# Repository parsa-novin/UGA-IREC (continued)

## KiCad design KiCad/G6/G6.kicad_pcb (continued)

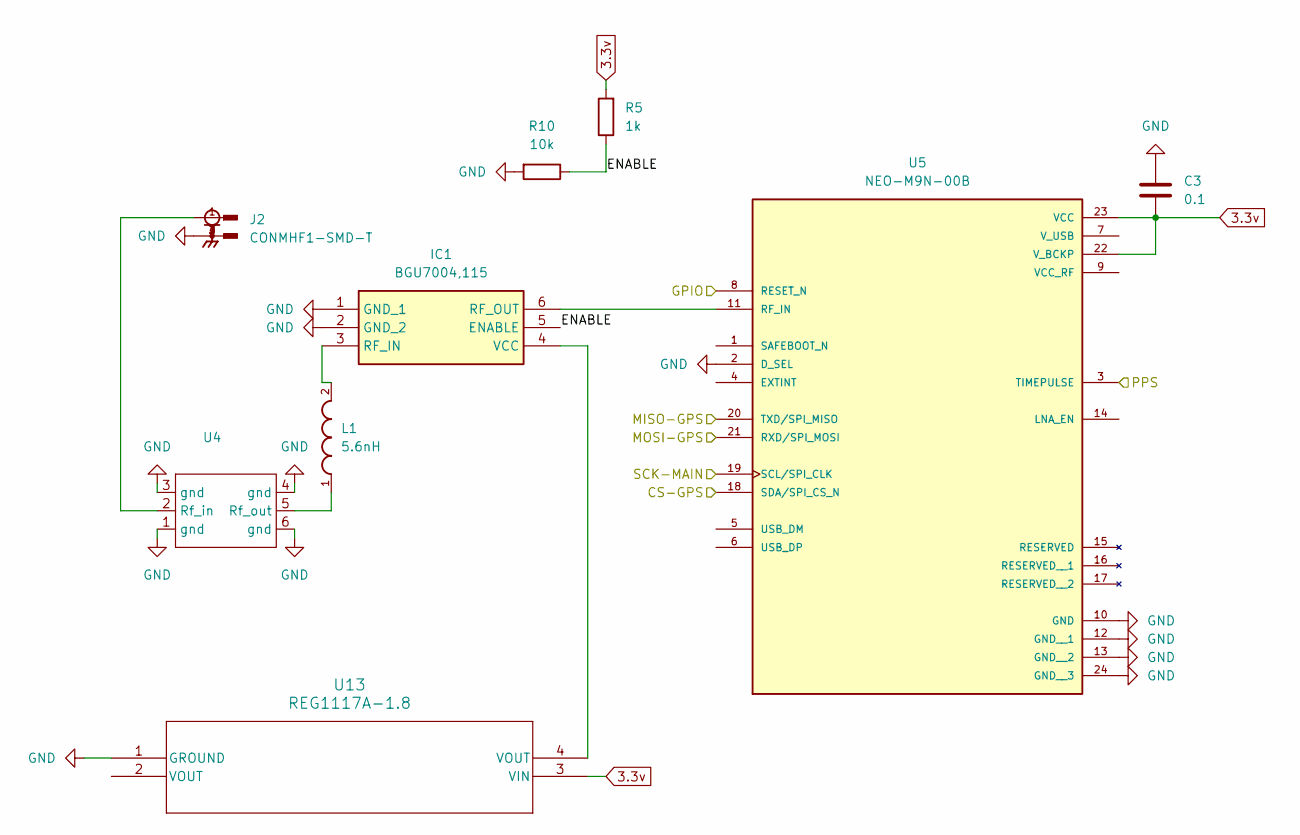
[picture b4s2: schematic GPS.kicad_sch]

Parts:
C3: 0.1; .1CAP_CC1206_YAG
IC1: BGU7004,115; BGU7004115; Manufacturer_Part_Number BGU7004,115; Mouser Part Number 771-BGU7004,115
J2: CONMHF1-SMD-T; TE_CONMHF1-SMD-T; PARTREV 09/22
L1: 5.6nH; L_1008_2520Metric
R5: 1k; R_0805_2012Metric
R10: 10k; R_0805_2012Metric
U4: RSF-1575.420-24000-3030-TR
U5: NEO-M9N-00B; XCVR_NEO-M9N-00B; PARTREV R05
U13: REG1117A-1.8; LDO1.8

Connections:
3.3v: C3.2, R5.2, U5.22 (V_BCKP), U5.23 (VCC), U13.3 (VIN); also elsewhere on the board
/BMI270/MISO-BMI: U5.20 (TXD/SPI_MISO); also elsewhere on the board
/BMI270/MOSI-BMI: U5.21 (RXD/SPI_MOSI); also elsewhere on the board
/GPS/CS-GPS: U5.18 (SDA/SPI_CS_N); also elsewhere on the board
/GPS/ENABLE: IC1.5 (ENABLE), R5.1, R10.1
/GPS/GPIO: U5.8 (RESET_N); also elsewhere on the board
/SCK-MAIN: U5.19 (SCL/SPI_CLK); also elsewhere on the board
GND: C3.1, IC1.1 (GND_1), IC1.2 (GND_2), J2.2, J2.3, J2.4, R10.2, U4.1 (gnd), U4.3 (gnd), U4.4 (gnd), U4.6 (gnd), U5.2 (D_SEL), U5.10 (GND), U5.12 (GND__1), U5.13 (GND__2), U5.24 (GND__3), U13.1 (GROUND); also elsewhere on the board
unnamed: IC1.3 (RF_IN), L1.2
unnamed: IC1.6 (RF_OUT), U5.11 (RF_IN)
unnamed: IC1.4 (VCC), U13.4 (VOUT)
unnamed: J2.1, U4.2 (Rf_in)
unnamed: L1.1, U4.5 (Rf_out)
PPS: U5.3 (TIMEPULSE); also elsewhere on the board

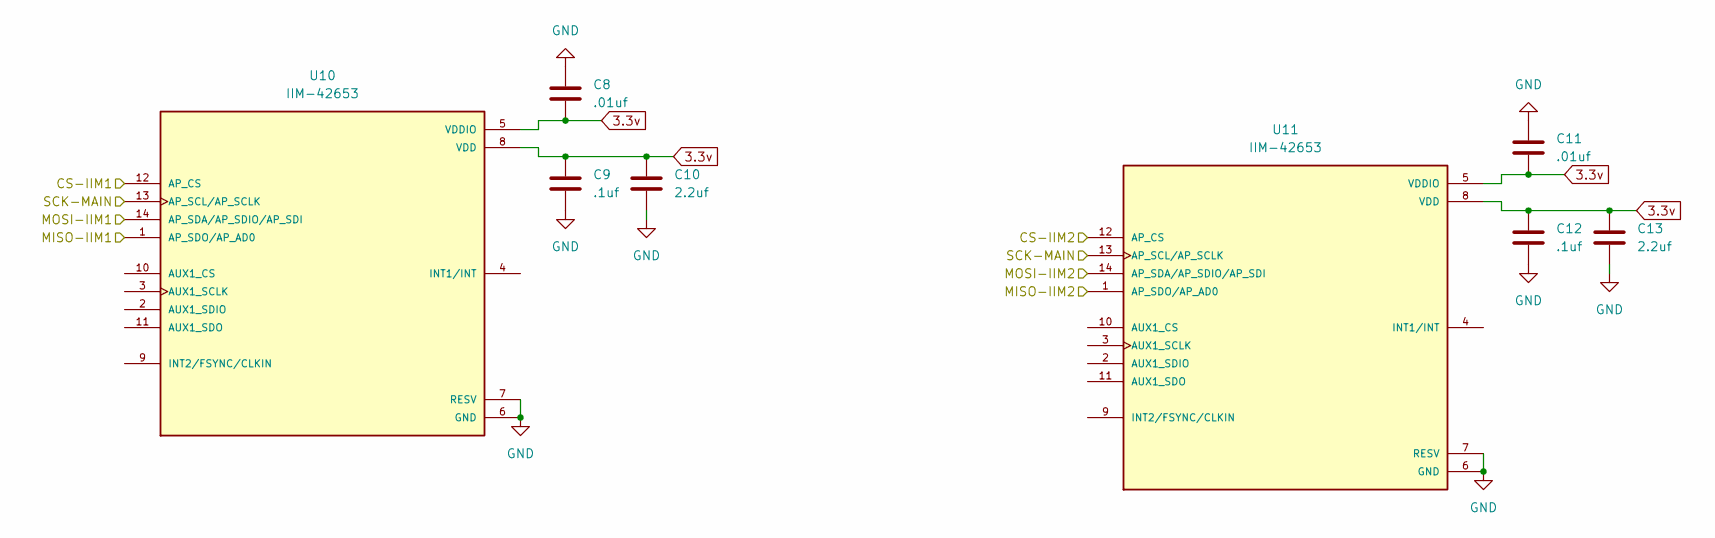
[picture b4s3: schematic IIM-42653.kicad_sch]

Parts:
C8, C11: .01uf; .01YAG_CC1206_YAG
C9, C12: .1uf; .1CAP_CC1206_YAG
C10, C13: 2.2uf; 2.2CAP_CC1206_YAG
U10, U11: IIM-42653; IIM42563; PARTREV 1.1

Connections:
3.3v: C8.2, C9.1, C10.1, C11.2, C12.1, C13.1, U10.5 (VDDIO), U10.8 (VDD), U11.5 (VDDIO), U11.8 (VDD); also elsewhere on the board
/BMI270/MISO-BMI: U10.1 (AP_SDO/AP_AD0), U11.1 (AP_SDO/AP_AD0); also elsewhere on the board
/BMI270/MOSI-BMI: U10.14 (AP_SDA/AP_SDIO/AP_SDI), U11.14 (AP_SDA/AP_SDIO/AP_SDI); also elsewhere on the board
/IIM-42653/CS-IIM1: U10.12 (AP_CS); also elsewhere on the board
/IIM-42653/CS-IIM2: U11.12 (AP_CS); also elsewhere on the board
/SCK-MAIN: U10.13 (AP_SCL/AP_SCLK), U11.13 (AP_SCL/AP_SCLK); also elsewhere on the board
GND: C8.1, C9.2, C10.2, C11.1, C12.2, C13.2, U10.6 (GND), U10.7 (RESV), U11.6 (GND), U11.7 (RESV); also elsewhere on the board

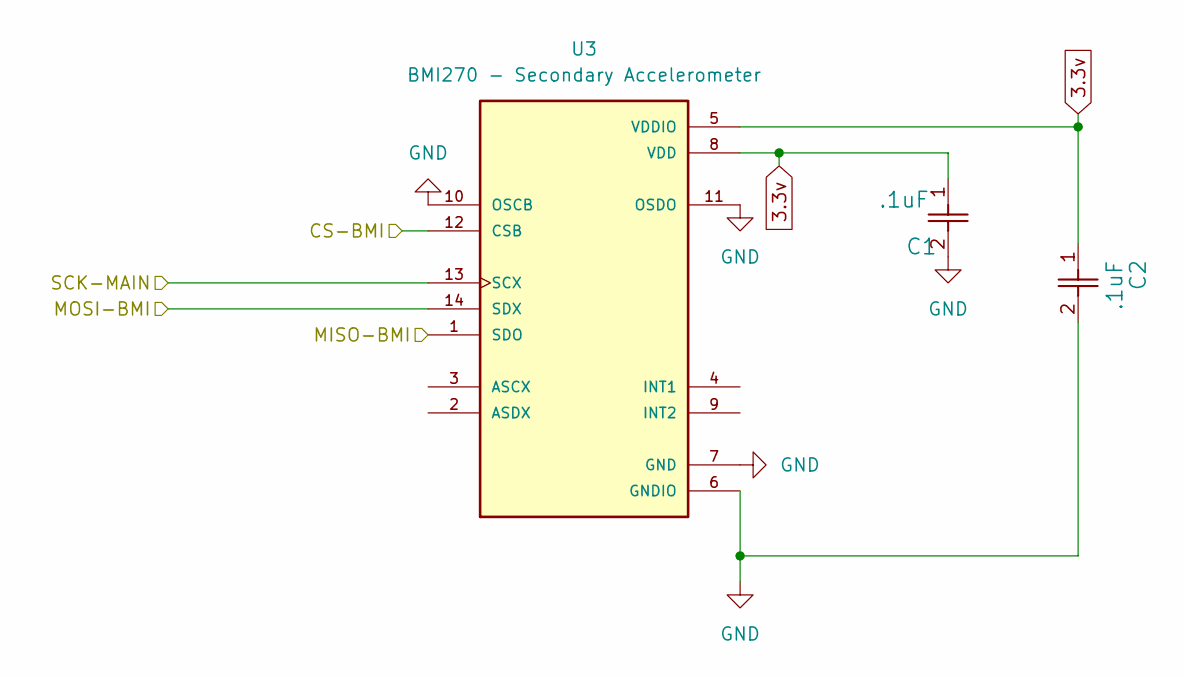
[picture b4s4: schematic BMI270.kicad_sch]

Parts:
C1, C2: .1uF; .1CAP_CC1206_YAG
U3: BMI270 - Secondary Accelerometer; XDCR_BMI270

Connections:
3.3v: C1.1, C2.1, U3.5 (VDDIO), U3.8 (VDD); also elsewhere on the board
/BMI270/CS-BMI: U3.12 (CSB); also elsewhere on the board
/BMI270/MISO-BMI: U3.1 (SDO); also elsewhere on the board
/BMI270/MOSI-BMI: U3.14 (SDX); also elsewhere on the board
/SCK-MAIN: U3.13 (SCX); also elsewhere on the board
GND: C1.2, C2.2, U3.6 (GNDIO), U3.7 (GND), U3.10 (OSCB), U3.11 (OSDO); also elsewhere on the board

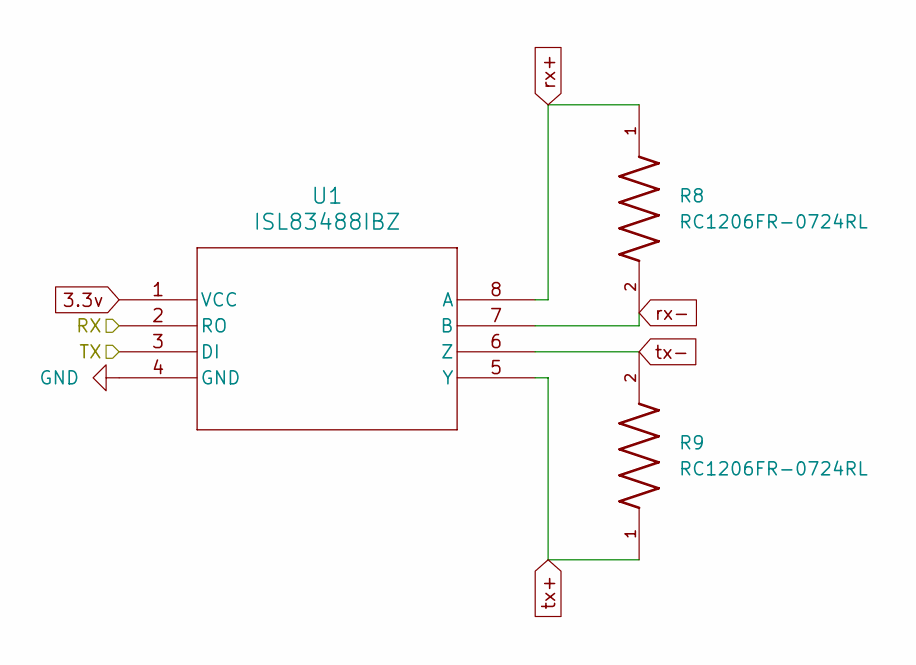
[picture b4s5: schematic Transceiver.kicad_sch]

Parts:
R8, R9: RC1206FR-0724RL; R_1206_3216Metric
U1: ISL83488IBZ; SOIC8_4X5_INR

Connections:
3.3v: U1.1 (VCC); also elsewhere on the board
/STM/RX: U1.2 (RO); also elsewhere on the board
/STM/TX: U1.3 (DI); also elsewhere on the board
GND: U1.4 (GND); also elsewhere on the board
rx+: R8.1, U1.8 (A); also elsewhere on the board
rx-: R8.2, U1.7 (B); also elsewhere on the board
tx+: R9.1, U1.5 (Y); also elsewhere on the board
tx-: R9.2, U1.6 (Z); also elsewhere on the board

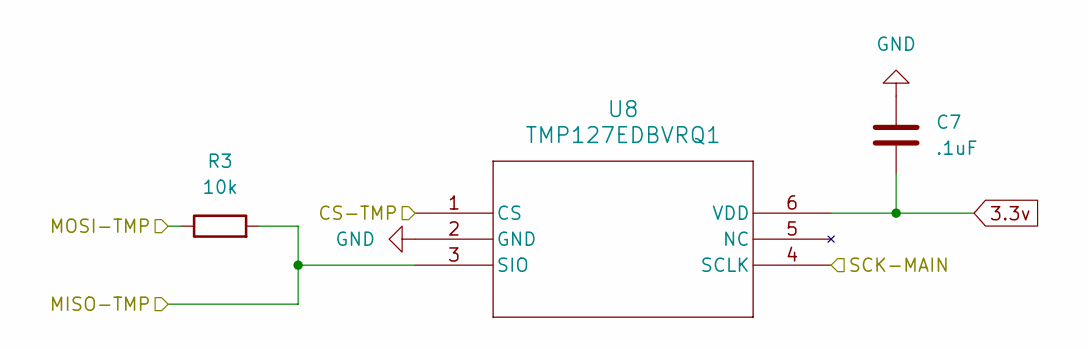
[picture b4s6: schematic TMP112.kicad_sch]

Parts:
C7: .1uF; .1CAP_CC1206_YAG
R3: 10k; 10kRC1206N_YAG
U8: TMP127EDBVRQ1; SOT23_DBV_TEX

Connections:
3.3v: C7.2, U8.6 (VDD); also elsewhere on the board
/BMI270/MISO-BMI: R3.2, U8.3 (SIO); also elsewhere on the board
/BMI270/MOSI-BMI: R3.1; also elsewhere on the board
/SCK-MAIN: U8.4 (SCLK); also elsewhere on the board
/STM/CS-TMP: U8.1 (CS); also elsewhere on the board
GND: C7.1, U8.2 (GND); also elsewhere on the board

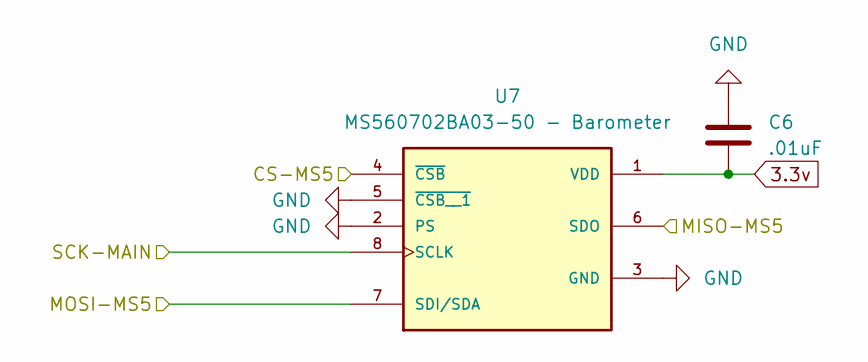
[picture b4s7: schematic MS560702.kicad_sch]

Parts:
C6: .01uF; .01YAG_CC1206_YAG
U7: MS560702BA03-50 - Barometer; SON125P300X500X100-8N

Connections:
3.3v: C6.2, U7.1 (VDD); also elsewhere on the board
/BMI270/MISO-BMI: U7.6 (SDO); also elsewhere on the board
/BMI270/MOSI-BMI: U7.7 (SDI/SDA); also elsewhere on the board
/MS560702/CS-MS5: U7.4 (~CSB); also elsewhere on the board
/SCK-MAIN: U7.8 (SCLK); also elsewhere on the board
GND: C6.1, U7.2 (PS), U7.3 (GND), U7.5 (~CSB__1); also elsewhere on the board

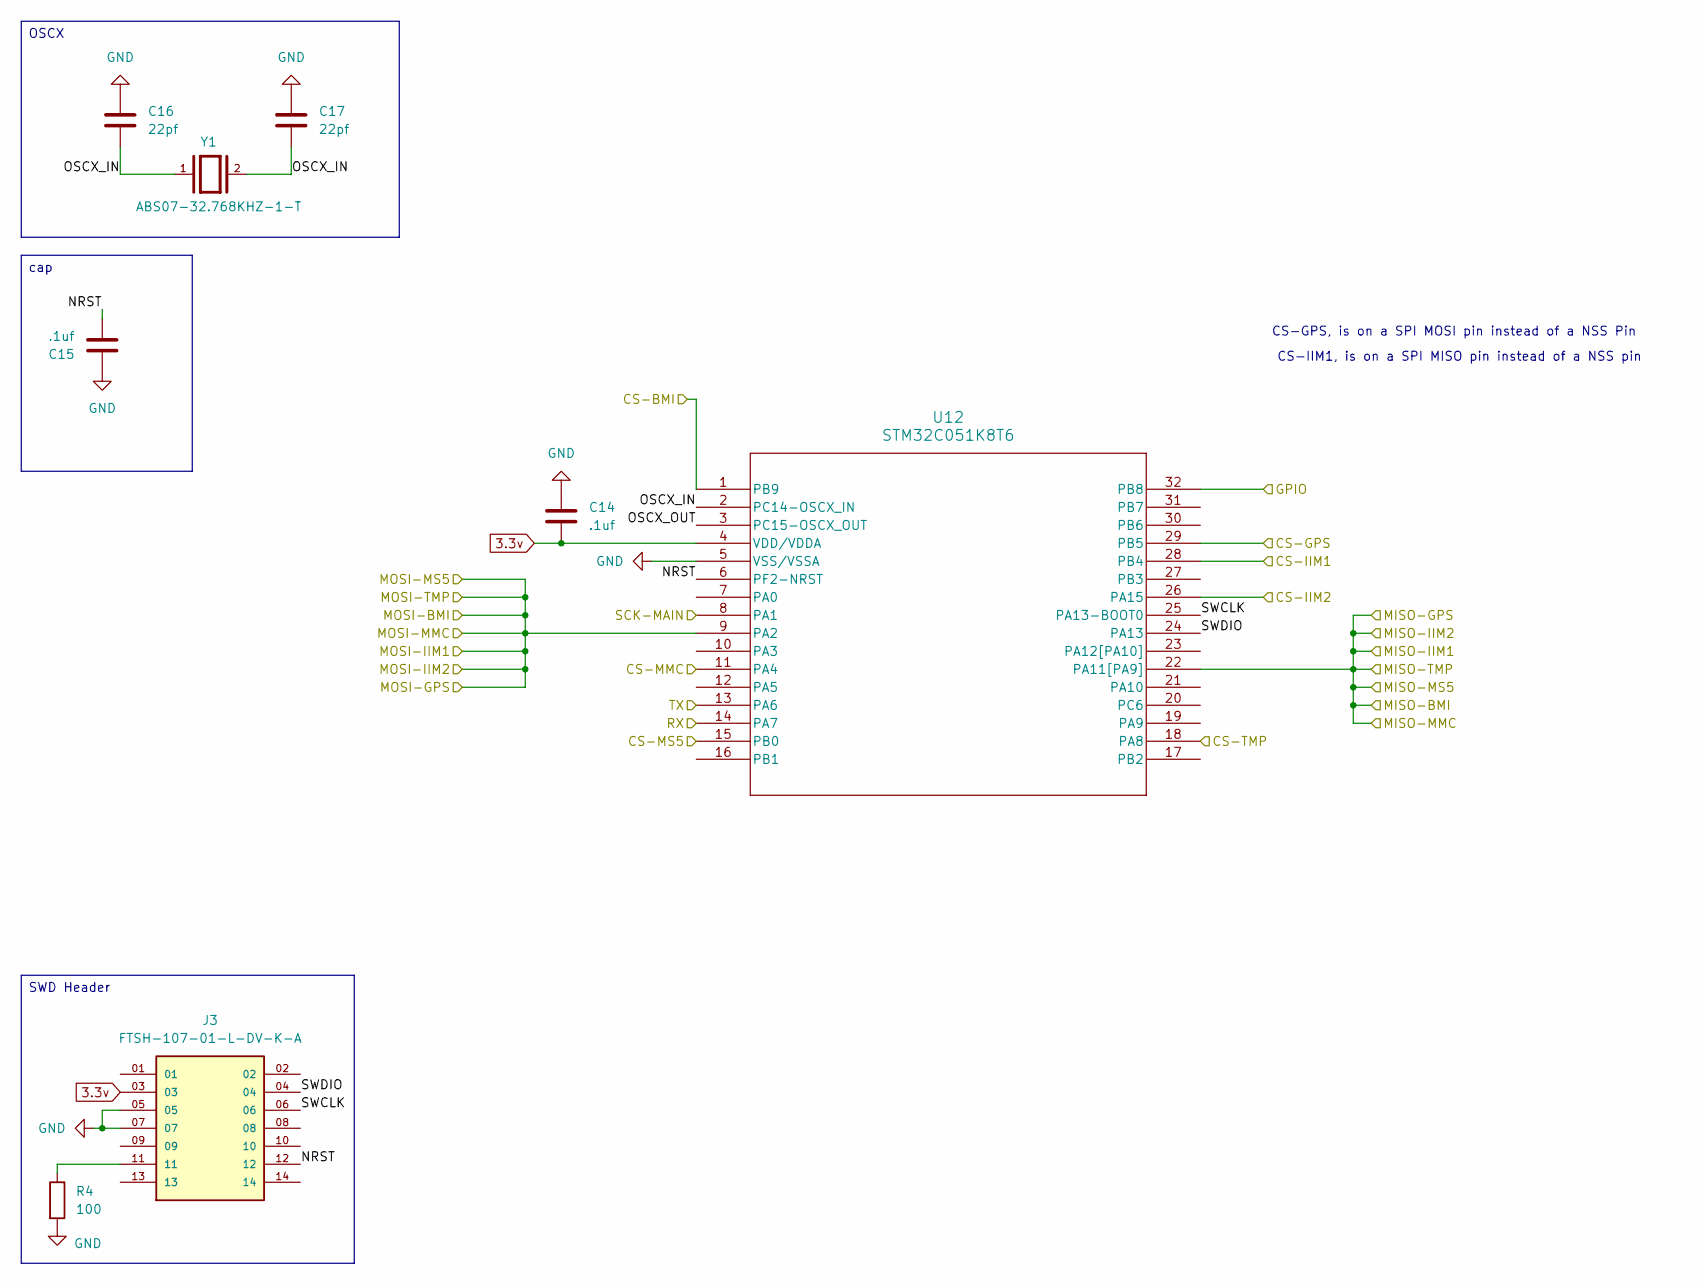
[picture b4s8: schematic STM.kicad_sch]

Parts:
C14, C15: .1uf; .1CAP_CC1206_YAG
C16, C17: 22pf; C_1206_3216Metric
J3: FTSH-107-01-L-DV-K-A; SAMTEC_FTSH-107-01-L-DV-K-A; PARTREV H
R4: 100; R_0805_2012Metric
U12: STM32C051K8T6; LQFP32_7x7_STM
Y1: ABS07-32.768KHZ-1-T; XTAL_ABS07-32.768KHZ-1-T; PARTREV 08.19.15; DigiKey_Part_Number 535-9808-1-ND

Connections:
3.3v: C14.2, J3.03, U12.4 (VDD/VDDA); also elsewhere on the board
/BMI270/CS-BMI: U12.1 (PB9); also elsewhere on the board
/BMI270/MISO-BMI: U12.22 (PA11[PA9]); also elsewhere on the board
/BMI270/MOSI-BMI: U12.9 (PA2); also elsewhere on the board
/GPS/CS-GPS: U12.29 (PB5); also elsewhere on the board
/GPS/GPIO: U12.32 (PB8); also elsewhere on the board
/IIM-42653/CS-IIM1: U12.28 (PB4); also elsewhere on the board
/IIM-42653/CS-IIM2: U12.26 (PA15); also elsewhere on the board
/MMC5983/CS-MMC: U12.11 (PA4); also elsewhere on the board
/MS560702/CS-MS5: U12.15 (PB0); also elsewhere on the board
/SCK-MAIN: U12.8 (PA1); also elsewhere on the board
/STM/CS-TMP: U12.18 (PA8); also elsewhere on the board
/STM/NRST: C15.2, J3.12, U12.6 (PF2-NRST)
/STM/OSCX_IN: C16.2, C17.2, U12.2 (PC14-OSCX_IN), Y1.1, Y1.2
/STM/OSCX_OUT: U12.3 (PC15-OSCX_OUT)
/STM/RX: U12.14 (PA7); also elsewhere on the board
/STM/SWCLK: J3.06, U12.25 (PA13-BOOT0)
/STM/SWDIO: J3.04, U12.24 (PA13)
/STM/TX: U12.13 (PA6); also elsewhere on the board
GND: C14.1, C15.1, C16.1, C17.1, J3.05, J3.07, R4.2, U12.5 (VSS/VSSA); also elsewhere on the board
unnamed: J3.11, R4.1

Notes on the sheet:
CS-IIM1, is on a SPI MISO pin instead of a NSS pin
CS-GPS, is on a SPI MOSI pin instead of a NSS Pin
cap
OSCX
SWD Header

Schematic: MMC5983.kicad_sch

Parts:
C4: 10uF; 10CAPC370195_195N_KEM-L
C5: 1uF; 1CAP_CS1206_YAG
U6: MMC5983MA-Magnetomer; PQFN50P300X300X100-16N; PARTREV A

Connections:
3.3v: C5.1, U6.2 (VDD), U6.13 (VDDIO); also elsewhere on the board
/BMI270/MISO-BMI: U6.5 (SPI_SDO); also elsewhere on the board
/BMI270/MOSI-BMI: U6.16 (SDA/SPI_SDI); also elsewhere on the board
/MMC5983/CS-MMC: U6.4 (~SPI_CS); also elsewhere on the board
/SCK-MAIN: U6.1 (SCL/SPI_SCK); also elsewhere on the board
GND: C4.2, C5.2, U6.9 (GND), U6.11 (GND__1); also elsewhere on the board
unnamed: C4.1, U6.10 (CAP)

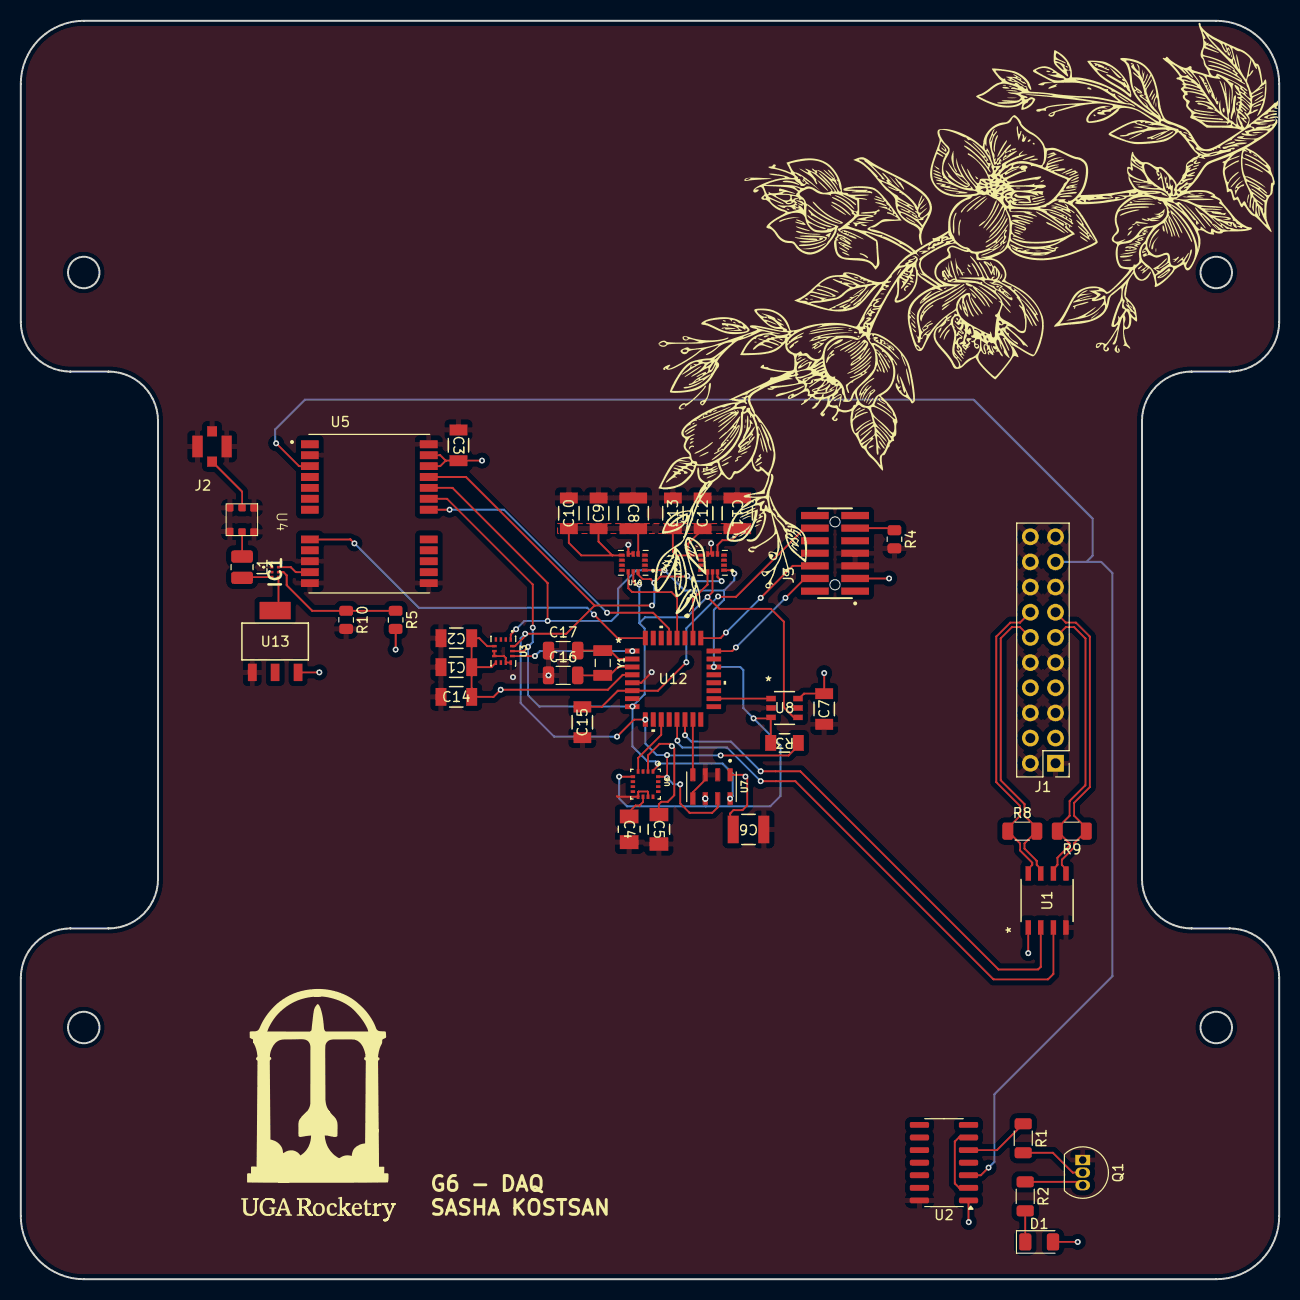
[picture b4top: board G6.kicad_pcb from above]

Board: 4 copper layers, 127.0 x 127.0 mm, 45 parts (0 on the bottom side), 38 nets.

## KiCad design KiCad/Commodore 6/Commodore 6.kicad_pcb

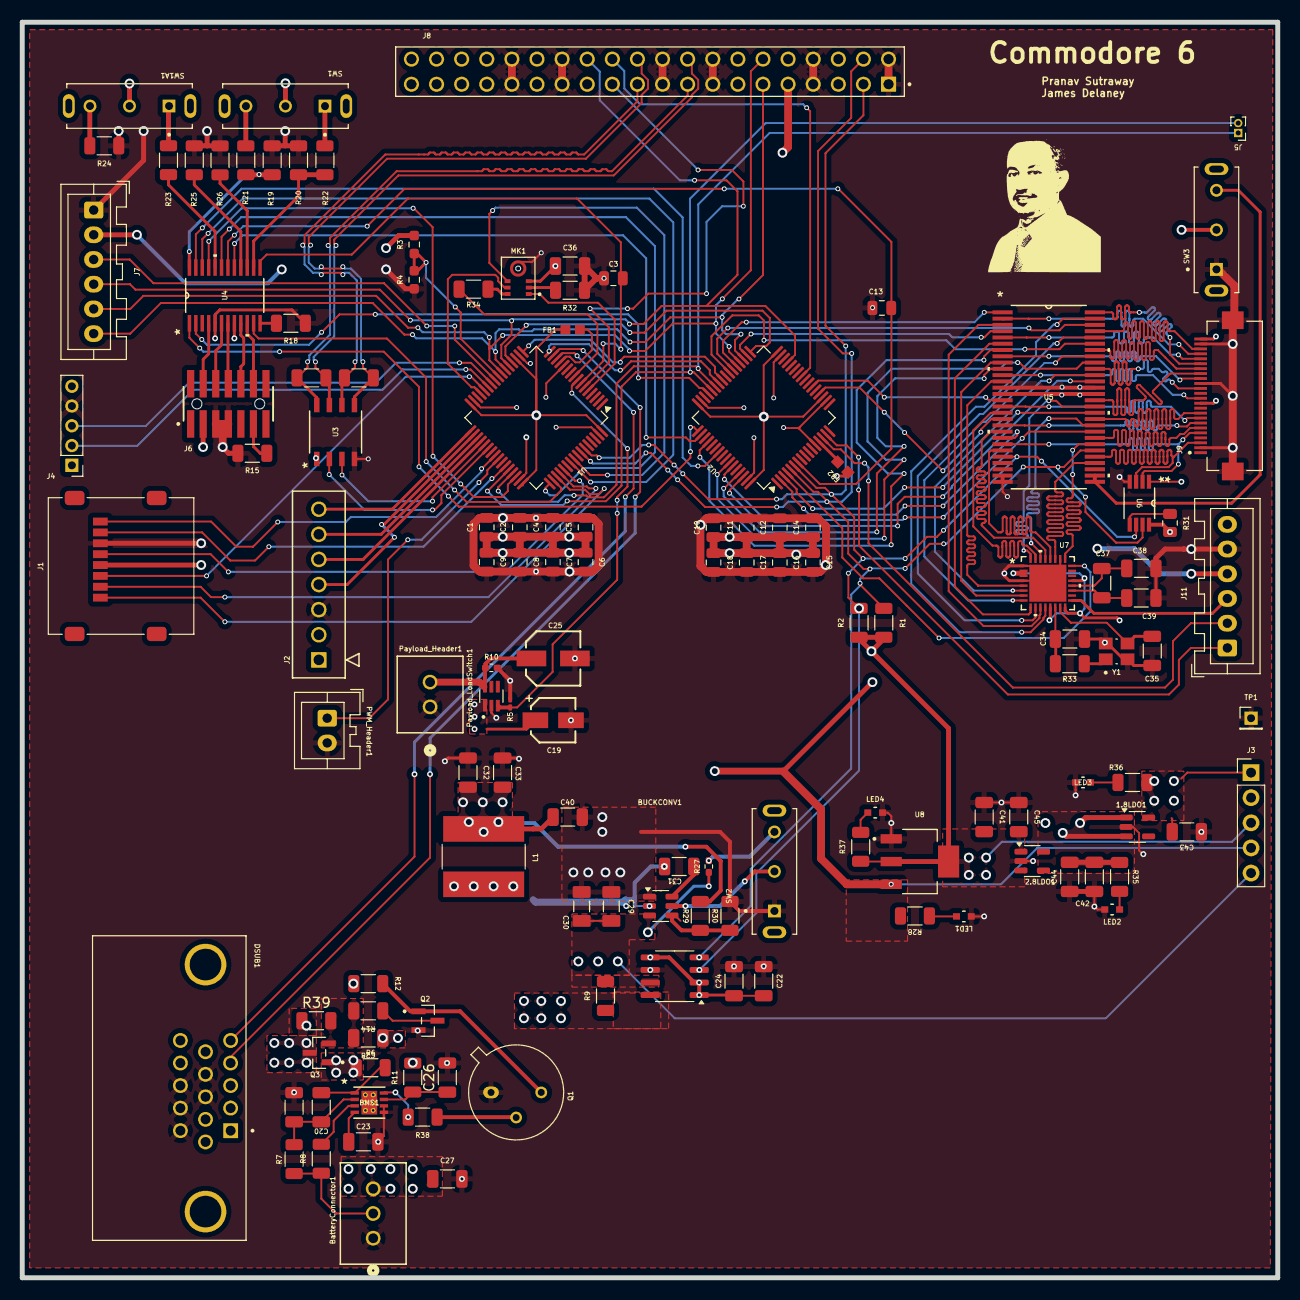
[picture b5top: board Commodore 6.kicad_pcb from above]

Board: 4 copper layers, 127.0 x 127.0 mm, 128 parts (0 on the bottom side), 155 nets.

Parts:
1.8LDO1: LP5907MFX-1.8; SOT-23-5
2.8LDO1: LP5907MFX-2.8; SOT-23-5
BMS1: BQ29209DRBR; DRB8_1P6X2P4
BUCKCONV1: TPS563200; SOT-23-6
BatteryConnector1: B03B-XASK-1; CONN_B03B-XASK-1_JST
C1, C10: 10uF; C_0805_2012Metric
C2, C3, C4, C5, C6, C11, C12, C13, C14, C15: 100nF; C_0805_2012Metric
C7, C16: 10nF; C_0805_2012Metric
C8, C9, C17, C18: 1uF; C_0805_2012Metric
C19: WCAP-ASLL_4X5.5/865060640001 1uf smd electrolytic; WCAP-ASLL_4X5.5_DXL_
C20, C21, C24, C26, C27, C28, C36, C37, C38, C39: 0.1uF; C_1206_3216Metric
C22: 10uF; C_1206_3216Metric
C23: 0.33uF; C_1206_3216Metric
C25: WCAP-ASLI_5X5.5/ 47uf electro; WCAP-ASLI_5X5.5_DXL_
C29, C30: CL31B106KAHNNNE/10uf; CAPC3216X180N
C31: 08053C104KAT2A/0.1uf; C_1206_3216Metric
C32, C33: CL10A226MP8NUNE/22uf; C_1206_3216Metric
C34, C35: 20nF; C_1206_3216Metric
C40, C41, C42, C43, C44, C45: CL10B105KP8NNNC 1uf; C_1206_3216Metric
Current_Monitor1: INA219AxD; SOIC-8_3.9x4.9mm_P1.27mm
DSUB1: ICD15S13E4GX00LF; AMPHENOL_ICD15S13E4GX00LF
FB1, FB2: BLM18KG121TN1D; BEADC1608X75N
J1: 472192001; microSD_HC_Molex_47219-2001
J2: PPTC071LFBN-RC; CONN_xPxC071LFBN-RC_SUL
J3: 6130XX11121_61300511121; PinHeader_1x05_P2.54mm_Vertical
J4: Conn_01x05_Pin; PinHeader_1x05_P2.00mm_Vertical
J5: Conn_01x02_Pin; PinHeader_1x02_P1.00mm_Vertical
J6: FTSH-107-01-L-DV-K-A; SAMTEC_FTSH-107-01-L-DV-K-A
J7, J11: Conn_01x06; JST_XA_B06B-XASK-1_1x06_P2.50mm_Vertical
J8: M20-6112045; HARWIN_M20-6112045
J9: FH12-24S-0.5SH_55_; HRS_FH12-24S-0.5SH_55_
L1: SRN8040-3R3Y/3.3uH; L_Bourns-SRN8040_8x8.15mm
LED1, LED2, LED3, LED4: LTST-C190KRKT; LED_LTST-C190_LTO
MK1: DMM-4026-B-I2S-R; MIC_DMM-4026-B-I2S-R
PWM_Header1: B02B-XASK-1LFSN; JST_XA_B02B-XASK-1_1x02_P2.50mm_Vertical
Payload_Header1: B02B-XASK-1LFSN; CONN_B02B-XASK-1LFSN_JST
Payload_LoadSwitch1: TPS22919DCKR; SOT65P210X110-6N
Q1: 2N2219; TO-39-3
Q2: NTR4501NT1G; SOT95P237X111-3N
Q3: PMOS; SOT95P237X111-3N
R1, R2: 20K; R_1206_3216Metric
R3: ERA-3VRW6801V 6.8k ohm; R_0603_1608Metric_Pad0.98x0.95mm_HandSolder
R4: ERA-3VRW3301V 3.3k ohm; R_0603_1608Metric_Pad0.98x0.95mm_HandSolder
R5: RC0201FR-0710KL/ 10k; R_0201_0603Metric_Pad0.64x0.40mm_HandSolder
R6: 160; R_1206_3216Metric
R7: 260; R_1206_3216Metric
R8, R11: 100; R_1206_3216Metric
R9: 2m; R_1206_3216Metric
R10: RC0402JR-071KL 1k; R_0402_1005Metric_Pad0.72x0.64mm_HandSolder
R12: 1k; R_1206_3216Metric
R14: 470k; R_1206_3216Metric
R15: 100R; R_1206_3216Metric
R16, R17: 68R; R_1206_3216Metric
R18, R21, R22, R23, R25, R26: 50R; R_1206_3216Metric
R19, R20, R24: 100K; R_1206_3216Metric
R27: 10k; R_0402_1005Metric_Pad0.72x0.64mm_HandSolder
R28: RC1206FR-07249RL/220ohm; R_1206_3216Metric
R29: RC0201FR-0756K2L/56.2K ohm; R_1206_3216Metric
R30: RC0201FR-0710KL/10kohm; R_1206_3216Metric
R31: 10K; R_0805_2012Metric
R32, R34: 10K; R_1206_3216Metric
R33: 750R; R_1206_3216Metric
R35, R37: RC0805FR-07150RL; R_1206_3216Metric
R36: ERJ-2RKF1000X; R_1206_3216Metric
R38: 10000; R_1206_3216Metric
R39: 330k; R_1206_3216Metric
SW1, SW1A1, SW2, SW3: SLW-1277545-3A-RA-N-D; SW_SLW-1277545-3A-RA-N-D
TP1: RCWCTE; PinHeader_1x01_P2.00mm_Vertical
U1: STM32H562RIT6; LQFP-64_10x10mm_P0.5mm
U2: STM32H7A3RIT6; LQFP-64_10x10mm_P0.5mm
U3: SN65HVD74DR; D8_TEX
U4: TS3A27518EIPWRQ1; PW24
U5: SN74CBT16233DLR; DL56
U6: PCA9507DP,118; DGK8
U7: ADV7280AWBCPZ; CP-32-12_ADI
U8: TLV1117LV33DCYR; VREG_TLV1117LV33DCYR
Y1: ABM8AIG-28.63636MHZ; XTAL_ABM8AIG-28.63636MHZ-12-2Z-T3

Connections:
1.8V: 1.8LDO1.5 (OUT), C43.2, J3.1, R36.1, U7.2 (DVDDIO), U7.3 (DVDD), U7.13 (DVDD), U7.16 (PVDD), U7.21 (AVDD)
8.4V_evil: BatteryConnector1.3, C27.1, C28.1, Current_Monitor1.8 (IN+), Q3.1 (D), R6.1, R9.1, R11.2, R12.2
+2.8V: 1.8LDO1.1 (IN), 1.8LDO1.3 (EN), 2.8LDO1.5 (OUT), C42.2, C44.2, J3.2, J9.11 (DOVDD1.8V), J9.24 (AFVDD2.8V), R35.1, U6.1 (VCCA)
+3.3V: 2.8LDO1.1 (IN), 2.8LDO1.3 (EN), C1.1, C2.1, C4.1, C5.1, C6.1, C7.1, C8.1, C9.1, C10.1, C11.1, C12.1, C14.1, C15.1, C16.1, C17.1, C18.1, C36.1, C41.2, C45.2, FB1.1, FB2.1, J1.4 (VDD), J2.2 (3V3), J3.3, J6.03 (T_VCC), J8.5, J8.6, MK1.3 (VDD), R1.1, R2.1, R31.1, R37.1, SW1.2, SW1A1.2, U1.19 (VDD), U1.32 (VDD), U1.48 (VDD), U1.64 (VDD), U2.19 (VDD), U2.32 (VDD), U2.48 (VDD), U2.64 (VDD), U3.1 (VCC), U4.8 (V+), U6.8 (VCCB), U8.2 (OUT_2), U8.4 (OUT_4)
+5V: C19.1, C22.1, C24.1, C32.2, C33.2, C40.2, Current_Monitor1.1 (A1), Current_Monitor1.2 (A0), Current_Monitor1.5 (VS), J2.1 (VIN), J3.4, J8.9, J8.10, J11.4, L1.1, Payload_LoadSwitch1.1 (IN), R28.2, R29.2, SW3.2, U5.14 (VCC), U5.43 (VCC), U8.3 (IN)
+8.4V: BUCKCONV1.3 (VIN), C29.2, C30.2, Current_Monitor1.7 (IN-), J3.5, J7.2, R3.2, R9.2, R27.1
/Power/Buck Converter/buck-vbst_cap: BUCKCONV1.2 (SW), C31.2, L1.2
/Power/bruh: C28.2, Q3.2 (G), R14.2, R39.2
/STM32/Camera/CAM_NTSC: J11.3, U7.17 (AIN1)
/STM32/Connectors/T_JTDI: J6.10 (T_JTDI/NC), U4.9 (COM4)
/STM32/Connectors/T_NRST: J6.12 (T_NRST), U4.10 (COM5)
/STM32/Connectors/T_SWCLK: J6.06 (T_JCLK/T_SWCLK), U4.6 (COM2)
/STM32/Connectors/T_SWDIO: J6.04 (T_JTMS/T_SWDIO), U4.4 (COM1)
/STM32/Connectors/T_SWO: J6.08 (T_JTDO/T_SWO), U4.7 (COM3)
/STM32/FLASH_CS: J2.7 (CS), U1.33 (PB12)
/STM32/FLASH_MISO: J2.6 (MOSI), U1.35 (PB14)
/STM32/FLASH_MOSI: J2.5 (MISO), U1.36 (PB15)
/STM32/FLASH_SCK: J2.4 (SCK), U1.34 (PB13)
/STM32/SD CLK: J1.5 (CLK), U1.53 (PC12)
/STM32/SD D1: J1.8 (DAT1), U1.40 (PC9)
/STM32/SD D2: J1.1 (DAT2), U1.51 (PC10)
/STM32/SD D3: J1.2 (CD/DAT3), U1.52 (PC11)
ADC_IN: R3.1, R4.2, U1.24 (PC4)
AIR_PWM: PWM_Header1.1, U1.41 (PA8)
CAM_D0: U2.37 (PC6), U5.1 (1A)
CAM_D1: U2.38 (PC7), U5.54 (2A)
CAM_D2: U2.34 (PB13), U5.4 (3A)
CAM_D3: U2.39 (PC9), U5.51 (4A)
CAM_D4: U2.52 (PC11), U5.7 (5A)
CAM_D5: U2.58 (PB6), U5.48 (6A)
CAM_D6: U2.61 (PB8), U5.10 (7A)
CAM_D7: U2.62 (PB9), U5.45 (8A)
CAM_HSYNC: U2.20 (PA4), U5.18 (11A)
CAM_PIXCLK: U2.22 (PA6), U5.15 (9A)
CAM_PWDN: U2.3 (PC14), U5.40 (10A)
CAM_RST: U2.2 (PC13), U5.21 (13A)
CAM_RX: J11.1, U2.15 (PA1)
CAM_TX: J11.2, U2.14 (PA0)
CAM_VSYNC: U2.59 (PB7), U5.37 (12A)
DCMI_D0: J9.19 (Y2), U5.56 (1B1)
DCMI_D1: J9.21 (Y3), U5.2 (2B1)
DCMI_D2: J9.22 (Y4), U5.53 (3B1)
DCMI_D3: J9.20 (Y5), U5.5 (4B1)
DCMI_D4: J9.18 (Y6), U5.50 (5B1)
DCMI_D5: J9.16 (Y7), U5.8 (6B1)
DCMI_D6: J9.14 (Y8), U5.47 (7B1)
DCMI_D7: J9.12 (Y9), U5.11 (8B1)
DCMI_HSYNC: J9.9 (HSYNC), U5.39 (11B1)
DCMI_PIXCLK: J9.17 (PCLK), U5.42 (9B1)
DCMI_PWDN: J9.8 (PWDN), U5.16 (10B1)
DCMI_RST: J9.6 (RST), U5.36 (13B1)
DCMI_SCL: J9.5 (SCL), U5.22 (14B1), U6.2 (SCLA)
DCMI_SDA: J9.3 (SDA), U5.33 (15B1), U6.3 (SDAA)
DCMI_VSYNC: J9.7 (VSYNC), U5.19 (12B1)
EGSE_RX: DSUB1.4, U1.15 (PA1)
EGSE_TX: DSUB1.5, U1.14 (PA0)
FDCAN_RX: J5.1, U1.45 (PA12), U2.43 (PA11)
FDCAN_TX: J5.2, U1.44 (PA11), U2.44 (PA12)
GND: U1.12 (VSSA), U1.18 (VSS), U1.31 (VSS), U1.47 (VSS), U1.63 (VSS), U2.12 (VSSA), U2.18 (VSS), U2.31 (VSS), U2.47 (VSS), U2.63 (VSS), U7.33 (GND)
GNDA: 1.8LDO1.2 (GND), 2.8LDO1.2 (GND), BMS1.5 (GND), BMS1.6 (*CB_EN), BUCKCONV1.1 (GND), BatteryConnector1.1, C1.2, C2.2, C3.1, C4.2, C5.2, C6.2, C7.2, C8.2, C9.2, C10.2, C11.2, C12.2, C13.1, C14.2, C15.2, C16.2, C17.2, C18.2, C19.2, C21.2, C22.2, C23.2, C24.2, C25.2, C26.2, C27.2, C29.1, C30.1, C32.1, C33.1, C34.1, C35.1, C36.2, C38.1, C39.1, C40.1, C41.1, C42.1, C43.1, C44.1, C45.1, Current_Monitor1.6 (GND), DSUB1.8, DSUB1.9, DSUB1.11, DSUB1.12, DSUB1.13, J1.6 (VSS), J2.3 (GND), J4.4, J6.05 (GND), J6.07 (GND), J7.1, J8.1, J8.2, J8.7, J8.8, J8.15, J8.16, J8.19, J8.20, J8.27, J8.28, J8.31, J8.32, J9.2 (AGND), J9.15 (GND), J9.23 (AF-GND), J9.P1 (SHIELD), J9.P2 (SHIELD__1), J11.5, LED1.1, LED2.1, LED3.1, LED4.1, MK1.4 (GND), PWM_Header1.2, Payload_Header1.1, Payload_LoadSwitch1.2 (GND), Q1.1 (E), Q2.2, R4.1, R5.1, R10.2, R15.1, R18.2, R19.1, R20.2, R24.2, R25.1, R26.1, R30.1, R32.2, SW2.1, SW3.1, TP1.1, U3.4 (GND), U4.5 (GND), U5.13 (GND), U5.27 (TEST1), U5.28 (TEST2), U5.44 (GND), U6.4 (GND), U7.1 (DGND), U7.4 (DGND), U7.26 (ALSB), U8.1 (GND), Y1.2 (GND), Y1.4 (GND)
GPIO: J8.24, J8.25, J8.29, J8.30, J8.33, J8.34, U2.25 (PC5)
GPS_PPS: J8.23, U1.6 (PH1)
H5_JTDI: U1.50 (PA15(JTDI)), U4.11 (NO1)
H5_NRST: C3.2, U1.7 (NRST), U4.13 (NO2)
H5_SWCLK: U1.49 (PA14(JTCK), U4.19 (NC5)
H5_SWDIO: U1.46 (PA13(JTMS), U4.21 (NC4)
H5_SWO: U1.55 (PB3(JTDO), U4.22 (NC6)
H7_JTDI: U2.50 (PA15), U4.17 (NO4)
H7_NRST: C13.2, U2.7 (NRST), U4.18 (NO5)
H7_SWCLK: U2.49 (PA14), U4.1 (NC2)
H7_SWDIO: U2.45 (PA13), U4.2 (NC1)
H7_SWO: U2.55 (PB3), U4.23 (NC3)
I2C_SCL: Current_Monitor1.4 (SCL), J8.4, R1.2, U1.58 (PB6), U2.5 (PH0), U5.34 (14A), U6.7 (SCLB)
I2C_SDA: Current_Monitor1.3 (SDA), J8.3, R2.2, U1.59 (PB7), U2.6 (PH1), U5.24 (15A), U6.6 (SDAB)
I2S_SCK: MK1.6 (SCK), U1.29 (PB10)
I2S_SD: R34.1, U1.9 (PC1)
I2S_WS: MK1.5 (WS), U1.56 (PB4(NJTRST))
MIC_LR: MK1.1 (LR), U1.5 (PH0)
M_TRANS_A_N: J8.18, R16.2, U3.7 (B)
M_TRANS_A_P: J8.17, R16.1, U3.8 (A)
M_TRANS_Y_N: J8.21, R17.1, U3.6 (Z)
M_TRANS_Y_P: J8.22, R17.2, U3.5 (Y)
NTSC_D0: U5.55 (1B2), U7.12 (P0)
NTSC_D1: U5.3 (2B2), U7.11 (P1)
NTSC_D2: U5.52 (3B2), U7.10 (P2)
NTSC_D3: U5.6 (4B2), U7.9 (P3)
NTSC_D4: U5.49 (5B2), U7.8 (P4)
NTSC_D5: U5.9 (6B2), U7.7 (P5)
NTSC_D6: U5.46 (7B2), U7.6
NTSC_D7: U5.12 (8B2), U7.5 (P7)
NTSC_HSYNC: U5.38 (11B2), U7.30 (HS)
NTSC_INTR: U2.4 (PC15), U7.24 (*INTRQ)
NTSC_PIXCLK: U5.41 (9B2), U7.32 (LLC)
NTSC_PWDN: U5.17 (10B2), U7.31 (*PWRDWN)
NTSC_RST: U5.35 (13B2), U7.25 (*RESET)
NTSC_SCL: U5.23 (14B2), U7.28 (SCLK)
NTSC_SDA: U5.32 (15B2), U7.27 (SDATA)
NTSC_VSYNC: U5.20 (12B2), U7.29 (VS/FIELD/SFL)
unnamed: BMS1.4 (CD), C23.1
unnamed: BMS1.8 (OUT), R38.2
unnamed: BMS1.2 (VC1), C20.2, C21.1, R7.2
unnamed: BMS1.3 (VC1_CB), R8.2
unnamed: BMS1.1 (VC2), C20.1, R6.2
unnamed: BMS1.7 (VDD), C26.1, R11.1
unnamed: BUCKCONV1.5 (EN), SW2.2
unnamed: BUCKCONV1.6 (VBST), C31.1
unnamed: BUCKCONV1.4 (VFB), R29.1, R30.2
unnamed: BatteryConnector1.2, R7.1, R8.1
unnamed: J6.11 (GNDDetect), R15.2
unnamed: LED1.2, R28.1
unnamed: LED2.2, R35.2
unnamed: LED3.2, R36.2
unnamed: LED4.2, R37.2
unnamed: MK1.2 (CONFIG), R32.1
unnamed: MK1.7 (SD), R34.2
unnamed: C25.1, Payload_Header1.2, Payload_LoadSwitch1.6 (VOUT), R10.1
unnamed: Q1.2 (B), R38.1
unnamed: Q1.3 (C), Q2.1, R12.1
unnamed: Q2.3, R14.1
unnamed: R21.1, SW1.3
unnamed: R22.1, SW1.1
unnamed: R23.2, SW1A1.1
unnamed: R24.1, SW1A1.3
unnamed: R27.2, SW2.3
unnamed: R33.2, Y1.1
unnamed: FB1.2, U1.13 (VDDA)
unnamed: FB2.2, U2.13 (VDDA)
unnamed: R23.1, U4.20 (*EN)
unnamed: R18.1, U4.12 (COM6)
unnamed: R19.2, R21.2, U4.24 (IN1)
unnamed: R20.1, R22.2, U4.14 (IN2)
unnamed: R26.2, U4.15 (NO3)
unnamed: R25.2, U4.16 (NO6)
unnamed: SW3.3, U5.29 (SEL2), U5.30 (SEL1)
unnamed: R31.2, U6.5 (EN)
unnamed: C37.1, C38.2, U7.20 (VREFN)
unnamed: C37.2, C39.2, U7.19 (VREFP)
unnamed: C35.2, U7.15 (XTALN), Y1.3
unnamed: C34.2, R33.1, U7.14 (XTALP)
Payload_Switch: Payload_LoadSwitch1.3 (ON), R5.2, U1.8 (PC0)
SD CMD: J1.3 (CMD), U1.28 (PB2)
SD D0: J1.7 (DAT0), U1.43 (PA10)
SPI_MISO: J7.6, U1.22 (PA6), U2.35 (PB14)
SPI_MOSI: J7.5, U1.23 (PA7), U2.36 (PB15)
SPI_NSS: U1.20 (PA4), U2.33 (PB12)
SPI_NSS_RADIO: J7.3, U1.25 (PC5)
SPI_SCK: J7.4, U1.21 (PA5), U2.29 (PB10)
UART_RX: J4.2, U1.27 (PB1)
UART_TRANS_RX: U1.38 (PC7), U3.2 (R)
UART_TRANS_TX: U1.37 (PC6), U3.3 (D)
UART_TX: J4.3, U1.26 (PB0)
USART_RX: U1.16 (PA2), U2.42 (PA10)
USART_TX: U1.17 (PA3), U2.41 (PA9)
VBATT: J8.13, J8.14
VOUT: DSUB1.1, DSUB1.2, DSUB1.3, DSUB1.6, DSUB1.7, Q3.3 (S), R39.1
